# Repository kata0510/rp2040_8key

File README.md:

# rp2040_8key
[RP2040で作る自作キーボード](https://booth.pm/ja/items/4444554)の第4章で設計したキーボード基板です。

RP2040を用いた8キーの自作キーボード基板です。

検証用のためケースなどは付属しません。RP2040を用いた実際の動作と部品実装例の参考としてご利用ください。

## ファームウェア
ファームウェアは以下のリポジトリの`rp2040_8key`ブランチにあります。Cloneし、ブランチを切り替えてからqmk flashを実行してください。

[https://github.com/kata0510/qmk_firmware/tree/rp2040_8key](https://github.com/kata0510/qmk_firmware/tree/rp2040_8key)

QMK Firmwareのビルド環境未作成の場合は、公式ドキュメントもしくは[RP2040で作る自作キーボード](https://booth.pm/ja/items/4444554)の第2章を参考に構築してください。

[https://docs.qmk.fm/#/newbs_getting_started](https://docs.qmk.fm/#/newbs_getting_started)

```
$ git switch rp2040_8key
$ qmk flash -kb rp2040_8key -km default
```

firmwareフォルダ内にあるファームウェアは書籍の参考用として用意しているものです。お手持ちのqmk_firmwareリポジトリの`keyboards/`以下にフォルダをコピーしても書き込み可能です。

## 基板データについて
基板データは`PCB/`フォルダ以下にあります。Kicad7閲覧することができます。

JLCPCBのPCB Assemblyサービスを想定した部品ファイル(BOM)と配置ファイル(CPL)は`gerver/`フォルダ内にあります。

部品の在庫状況は日々返送するため、在庫無しの場合は同じ性能の部品を選択して製造してください。

## 不具合/問い合わせ
基板の不具合、お問い合わせに関しては以下のメールアドレス、もしくはDiscord(yuchi51)までご連絡ください。
```
yuchi.kbd@gmail.com
```

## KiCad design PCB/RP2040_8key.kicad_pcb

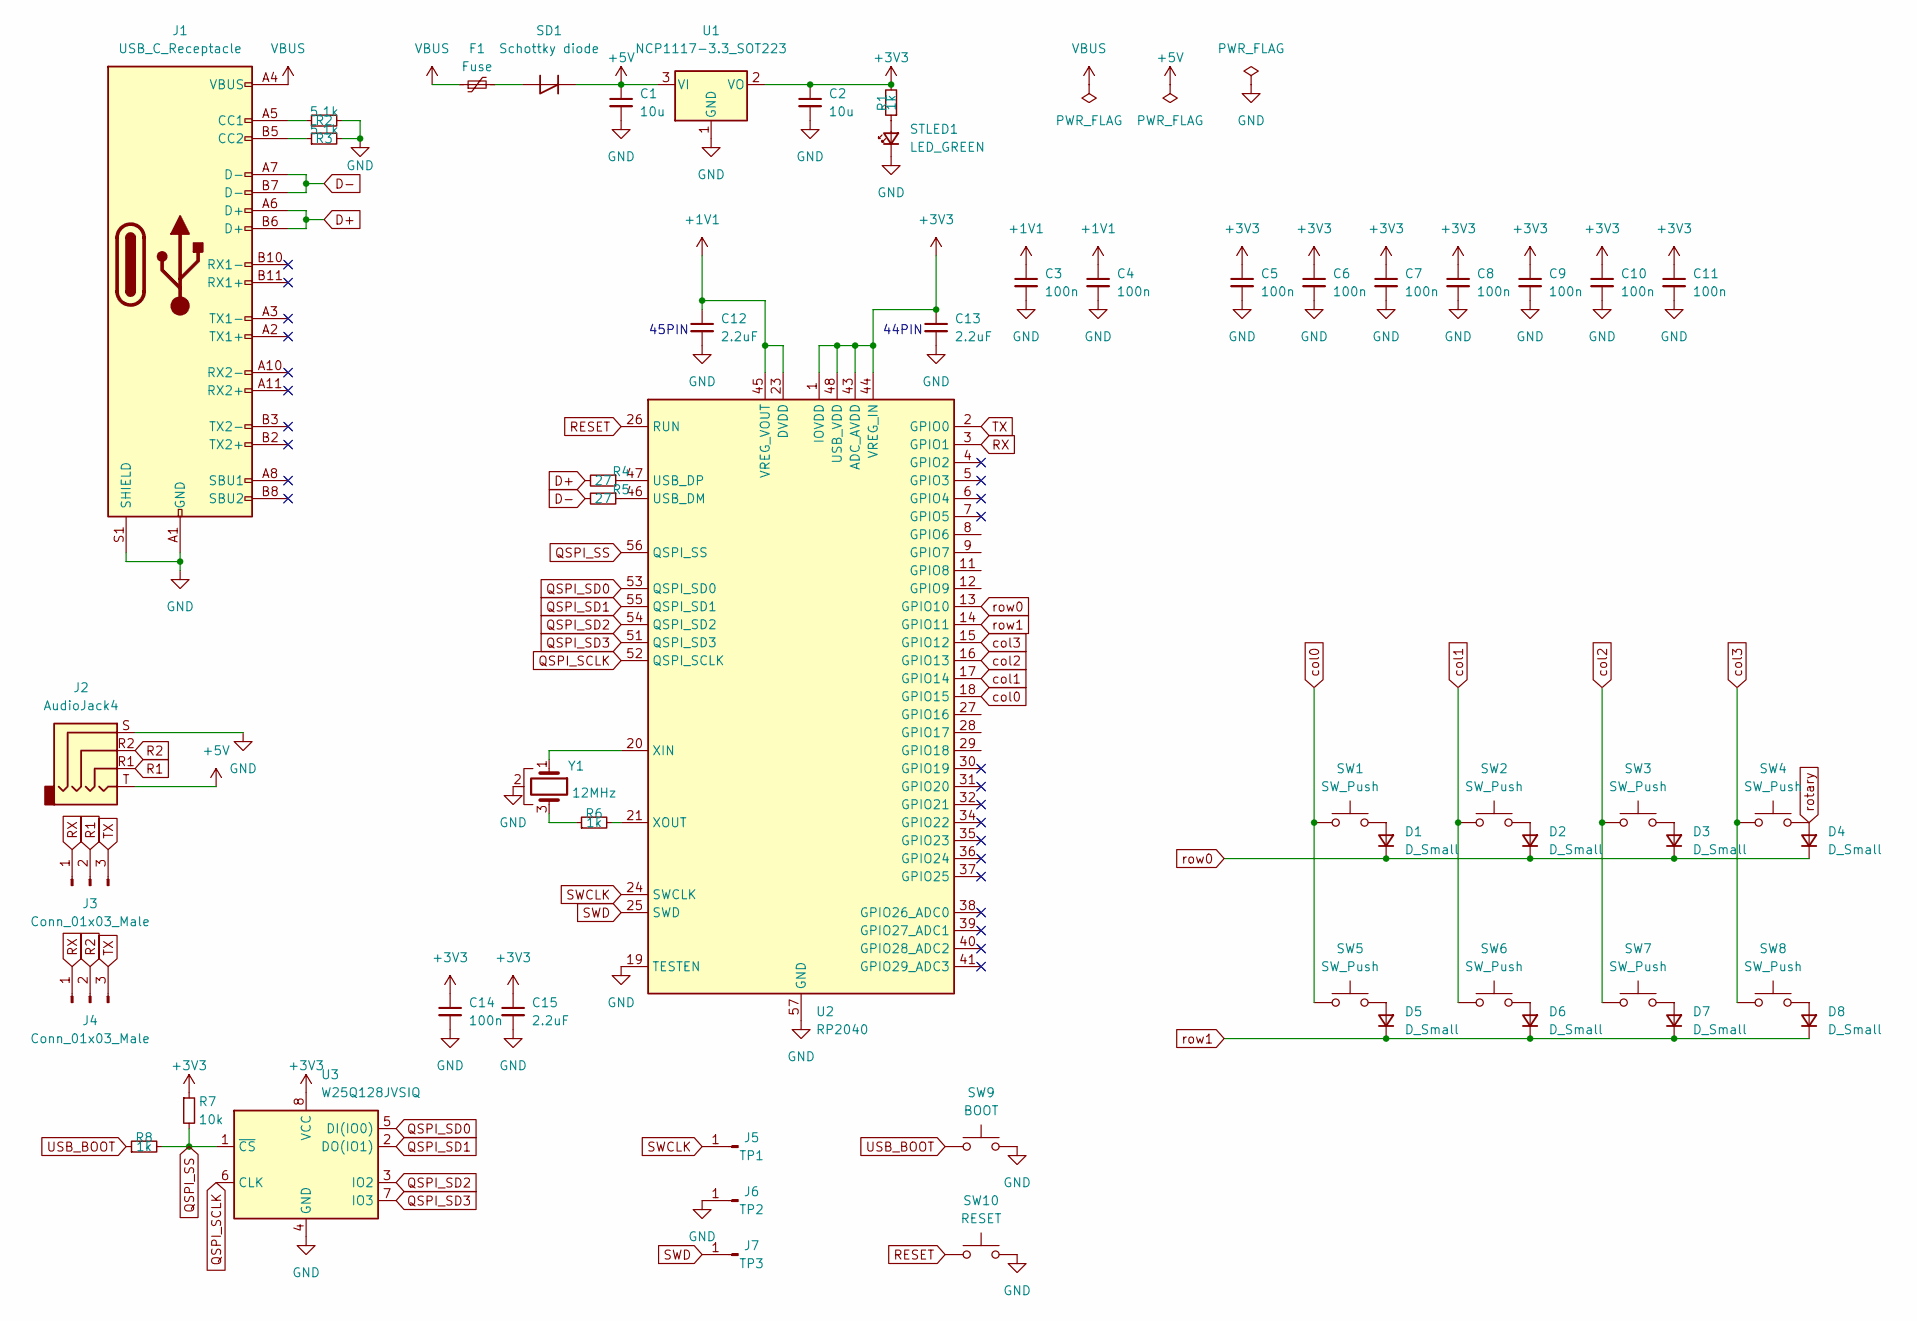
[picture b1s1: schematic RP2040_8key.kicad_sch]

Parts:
C1, C2: 10u; C_1206_3216Metric
C3, C4, C5, C6, C7, C8, C9, C10, C11, C14: 100n; C_0402_1005Metric
C12, C13, C15: 2.2uF; C_0402_1005Metric
D1, D2, D3, D4, D5, D6, D7, D8: D_Small; D_SOD-123
F1: Fuse; Fuse_0603_1608Metric; LCSC C122965
J1: USB_C_Receptacle; USB_C_Receptacle_HRO_TYPE-C-31-M-12
J2: AudioJack4; PJ-320
J3, J4: Conn_01x03_Male; SolderJumper-3_P1.3mm_Open_Pad1.0x1.5mm_NumberLabels
J5: TP1; TestPoint_Pad_D1.0mm
J6: TP2; TestPoint_Pad_D1.0mm
J7: TP3; TestPoint_Pad_D1.0mm
R1, R6, R8: 1k; R_0402_1005Metric
R2, R3: 5.1k; R_0402_1005Metric
R4, R5: 27; R_0402_1005Metric
R7: 10k; R_0402_1005Metric
SD1: Schottky diode; D_SOD-123
STLED1: LED_GREEN; LED_0402_1005Metric
SW1, SW2, SW3, SW4, SW5, SW6, SW7, SW8: SW_Push; MX_HOLE
SW9: BOOT; SW_SPST_PTS810
SW10: RESET; SW_SPST_PTS810
U1: NCP1117-3.3_SOT223; SOT-223
U2: RP2040; QFN-56-1EP_7x7mm_P0.4mm_EP3.2x3.2mm
U3: W25Q128JVSIQ; WSON-8-1EP_6x5mm_P1.27mm_EP3.4x4.3mm
Y1: 12MHz; Resonator_SMD_Murata_CSTxExxV-3Pin_3.0x1.1mm

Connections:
+1V1: C3.1, C4.1, C12.1, U2.23 (DVDD), U2.45 (VREG_VOUT), U2.50 (DVDD)
+3V3: C2.1, C5.1, C6.1, C7.1, C8.1, C9.1, C10.1, C11.1, C13.1, C14.1, C15.1, R1.2, R7.1, U1.2 (VO), U2.1 (IOVDD), U2.10 (IOVDD), U2.22 (IOVDD), U2.33 (IOVDD), U2.42 (IOVDD), U2.43 (ADC_AVDD), U2.44 (VREG_IN), U2.48 (USB_VDD), U2.49 (IOVDD), U3.8 (VCC)
+5V: C1.1, J2.T, SD1.1 (K), U1.3 (VI)
D+: J1.A6 (D+), J1.B6 (D+), R4.2
D-: J1.A7 (D-), J1.B7 (D-), R5.2
GND: C1.2, C2.2, C3.2, C4.2, C5.2, C6.2, C7.2, C8.2, C9.2, C10.2, C11.2, C12.2, C13.2, C14.2, C15.2, J1.A1 (GND), J1.A12 (GND), J1.B1 (GND), J1.B12 (GND), J1.S1 (SHIELD), J2.S, J6.1, R2.2, R3.2, STLED1.1 (K), SW9.2, SW10.2, U1.1 (GND), U2.19 (TESTEN), U2.57 (GND), U3.4 (GND), Y1.2
unnamed: D1.2 (A), SW1.2
unnamed: D2.2 (A), SW2.2
unnamed: D3.2 (A), SW3.2
unnamed: D5.2 (A), SW5.2
unnamed: D6.2 (A), SW6.2
unnamed: D7.2 (A), SW7.2
unnamed: D8.2 (A), SW8.2
unnamed: J1.A5 (CC1), R2.1
unnamed: J1.B5 (CC2), R3.1
unnamed: R6.1, Y1.3
unnamed: F1.2, SD1.2 (A)
unnamed: R1.1, STLED1.2 (A)
unnamed: R5.1, U2.46 (USB_DM)
unnamed: R4.1, U2.47 (USB_DP)
unnamed: U2.20 (XIN), Y1.1
unnamed: R6.2, U2.21 (XOUT)
QSPI_SCLK: U2.52 (QSPI_SCLK), U3.6 (CLK)
QSPI_SD0: U2.53 (QSPI_SD0), U3.5 (DI(IO0))
QSPI_SD1: U2.55 (QSPI_SD1), U3.2 (DO(IO1))
QSPI_SD2: U2.54 (QSPI_SD2), U3.3 (IO2)
QSPI_SD3: U2.51 (QSPI_SD3), U3.7 (IO3)
QSPI_SS: R7.2, R8.2, U2.56 (QSPI_SS), U3.1 (~CS)
R1: J2.R1, J3.2
R2: J2.R2, J4.2
RESET: SW10.1, U2.26 (RUN)
RX: J3.1, J4.1, U2.3 (GPIO1)
SWCLK: J5.1, U2.24 (SWCLK)
SWD: J7.1, U2.25 (SWD)
TX: J3.3, J4.3, U2.2 (GPIO0)
USB_BOOT: R8.1, SW9.1
VBUS: F1.1, J1.A4 (VBUS), J1.A9 (VBUS), J1.B4 (VBUS), J1.B9 (VBUS)
col0: SW1.1, SW5.1, U2.18 (GPIO15)
col1: SW2.1, SW6.1, U2.17 (GPIO14)
col2: SW3.1, SW7.1, U2.16 (GPIO13)
col3: SW4.1, SW8.1, U2.15 (GPIO12)
rotary: D4.2 (A), SW4.2
row0: D1.1 (K), D2.1 (K), D3.1 (K), D4.1 (K), U2.13 (GPIO10)
row1: D5.1 (K), D6.1 (K), D7.1 (K), D8.1 (K), U2.14 (GPIO11)

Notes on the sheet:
45PIN
44PIN

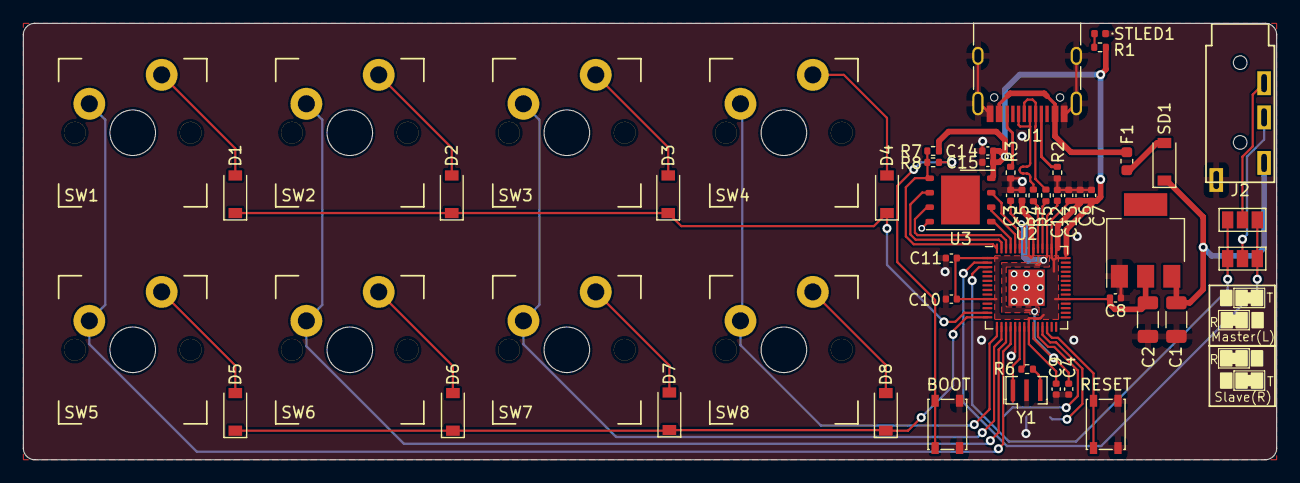
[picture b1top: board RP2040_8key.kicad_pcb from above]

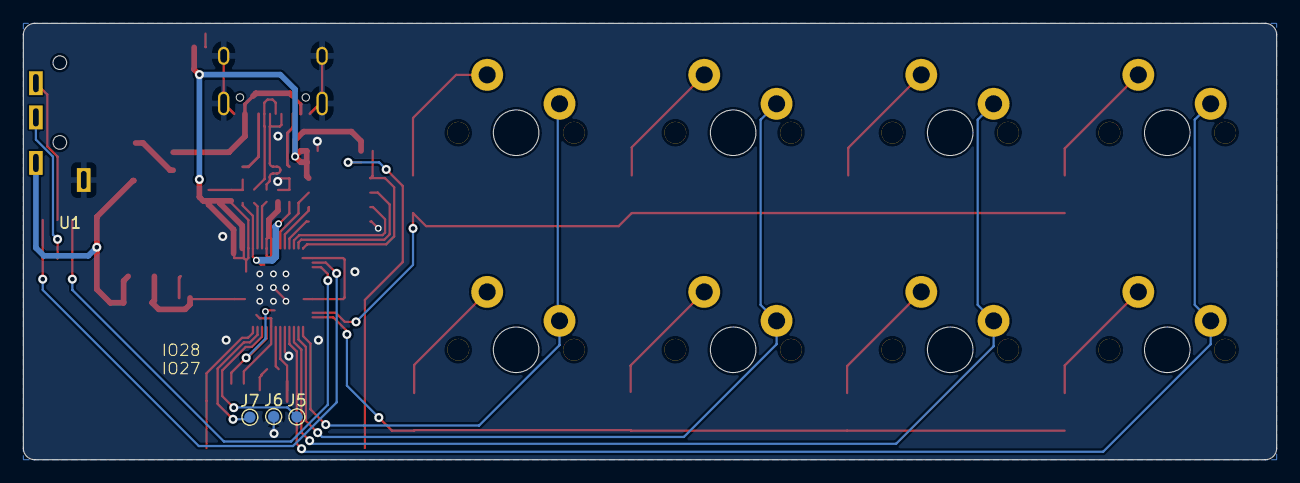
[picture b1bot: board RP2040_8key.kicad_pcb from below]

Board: 2 copper layers, 110.0 x 38.3 mm, 55 parts (3 on the bottom side), 44 nets.

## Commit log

2022-12-26 Add kicad files
2022-12-30 Add firmware gerber
2023-02-21 fix bom
2023-12-29 Update 2023Version
2023-12-30 breadboardのファームウェアは削除
2023-12-30 Create LICENSE
2023-12-30 keymap_update
2023-12-30 基板データを移動
